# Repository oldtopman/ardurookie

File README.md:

ardurookie
====
----
A simple, cheap board for the ATmega328 chips and compatibles.

This is Open Source Hardware, CC-BY-SA 4.0

See docs/overview.txt for more information.

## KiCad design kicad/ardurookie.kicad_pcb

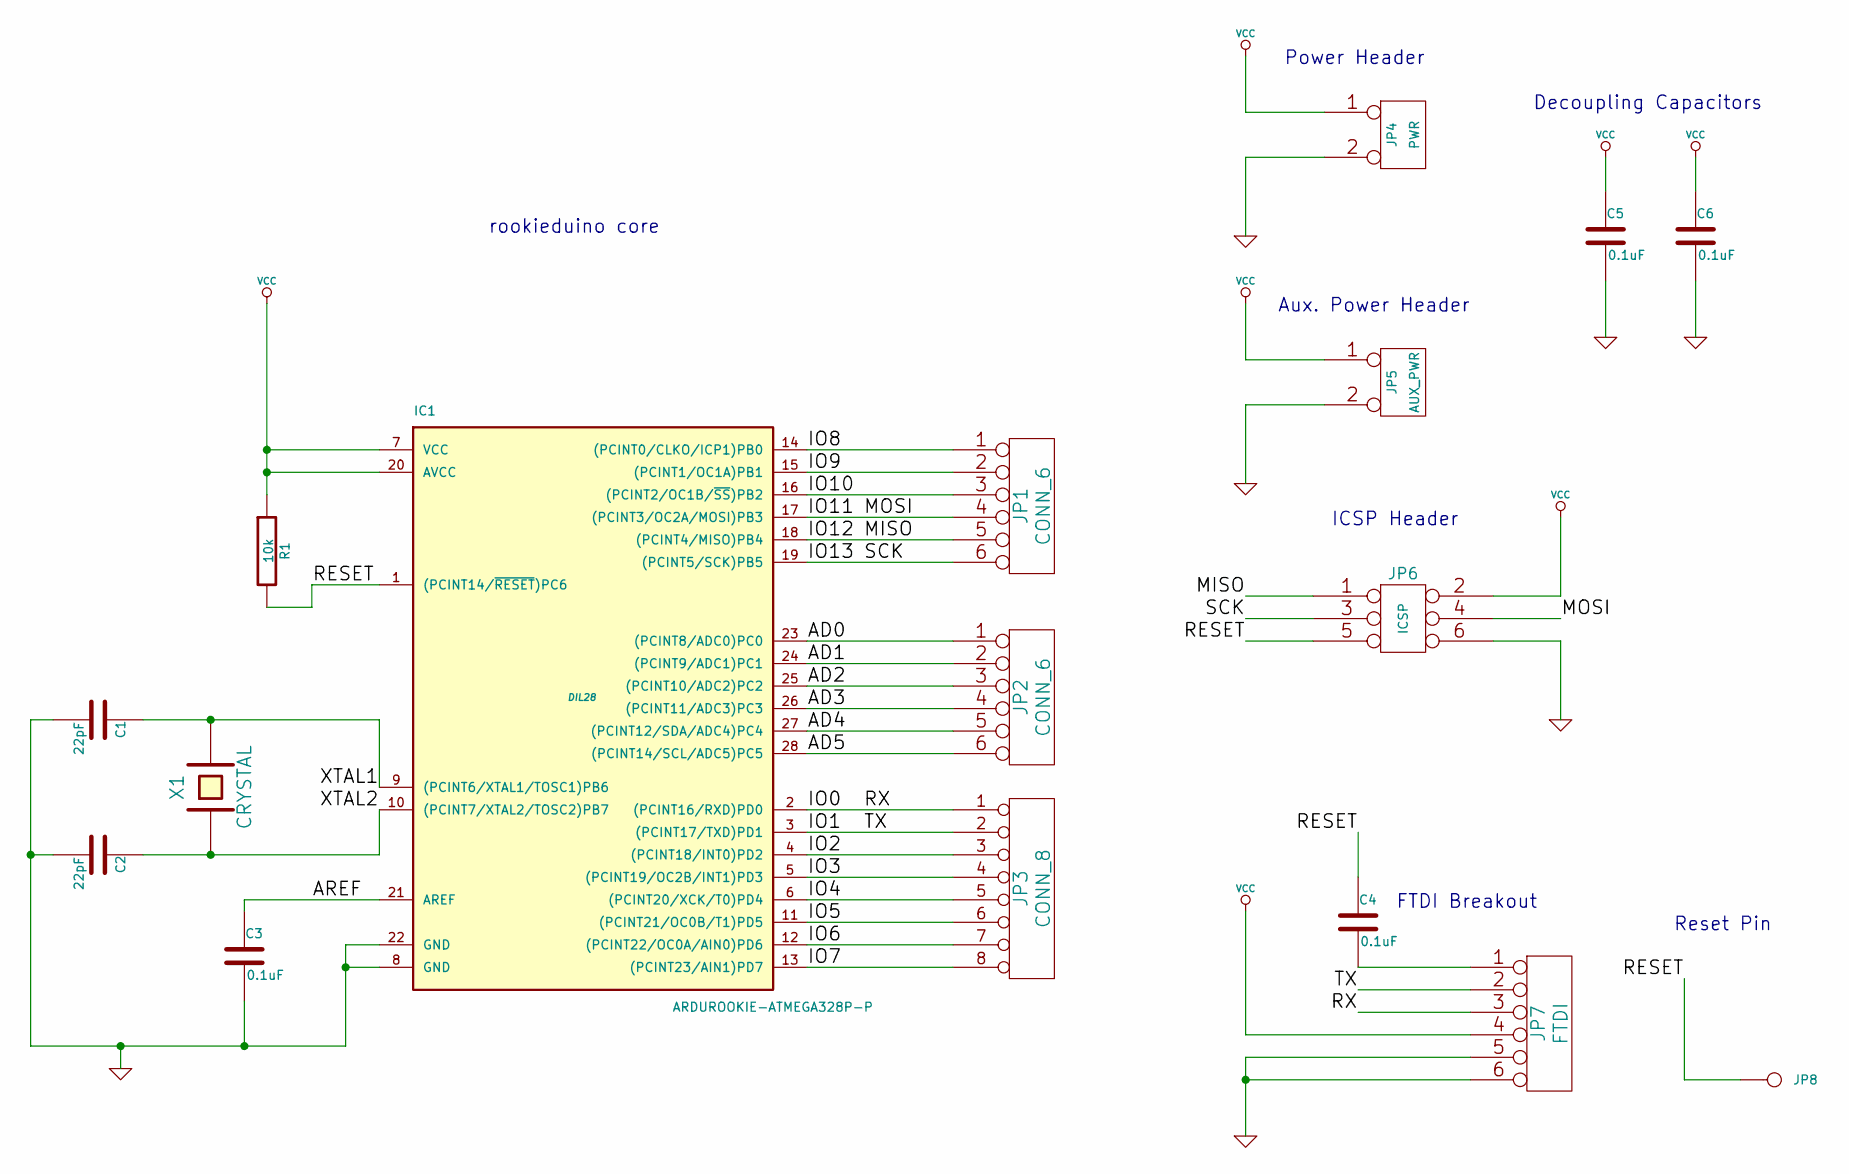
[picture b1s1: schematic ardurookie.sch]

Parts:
C1, C2: 22pF
C3, C4, C5, C6: 0.1uF
IC1: ARDUROOKIE-ATMEGA328P-P; DIL28
JP1, JP2: CONN_6
JP3: CONN_8
JP4: PWR
JP5: AUX_PWR
JP6: ICSP
JP7: FTDI
JP8: RST
R1: 10k
X1: CRYSTAL

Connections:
/AD0: IC1.23 ((PCINT8/ADC0)PC0), JP2.1
/AD1: IC1.24 ((PCINT9/ADC1)PC1), JP2.2
/AD2: IC1.25 ((PCINT10/ADC2)PC2), JP2.3
/AD3: IC1.26 ((PCINT11/ADC3)PC3), JP2.4
/AD4: IC1.27 ((PCINT12/SDA/ADC4)PC4), JP2.5
/AD5: IC1.28 ((PCINT14/SCL/ADC5)PC5), JP2.6
/AREF: C3.1, IC1.21 (AREF)
/IO0: IC1.2 ((PCINT16/RXD)PD0), JP3.1, JP7.3
/IO1: IC1.3 ((PCINT17/TXD)PD1), JP3.2, JP7.2
/IO2: IC1.4 ((PCINT18/INT0)PD2), JP3.3
/IO3: IC1.5 ((PCINT19/OC2B/INT1)PD3), JP3.4
/IO4: IC1.6 ((PCINT20/XCK/T0)PD4), JP3.5
/IO5: IC1.11 ((PCINT21/OC0B/T1)PD5), JP3.6
/IO6: IC1.12 ((PCINT22/OC0A/AIN0)PD6), JP3.7
/IO7: IC1.13 ((PCINT23/AIN1)PD7), JP3.8
/IO8: IC1.14 ((PCINT0/CLKO/ICP1)PB0), JP1.1
/IO9: IC1.15 ((PCINT1/OC1A)PB1), JP1.2
/IO10: IC1.16 ((PCINT2/OC1B/~SS~)PB2), JP1.3
/IO11: IC1.17 ((PCINT3/OC2A/MOSI)PB3), JP1.4, JP6.4
/IO12: IC1.18 ((PCINT4/MISO)PB4), JP1.5, JP6.1
/IO13: IC1.19 ((PCINT5/SCK)PB5), JP1.6, JP6.3
/RESET: C4.1, IC1.1 ((PCINT14/~RESET~)PC6), JP6.5, JP8.1, R1.2
/XTAL1: C1.1, IC1.9 ((PCINT6/XTAL1/TOSC1)PB6), X1.2
/XTAL2: C2.1, IC1.10 ((PCINT7/XTAL2/TOSC2)PB7), X1.1
GND: C1.2, C2.2, C3.2, C5.2, C6.2, IC1.8 (GND), IC1.22 (GND), JP4.2 (PM), JP5.2 (PM), JP6.6, JP7.5, JP7.6
unnamed: C4.2, JP7.1
VCC: C5.1, C6.1, IC1.7 (VCC), IC1.20 (AVCC), JP4.1, JP5.1, JP6.2, JP7.4, R1.1

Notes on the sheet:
Decoupling Capacitors
Power Header
ICSP Header
FTDI Breakout
rookieduino core
Aux. Power Header
Reset Pin

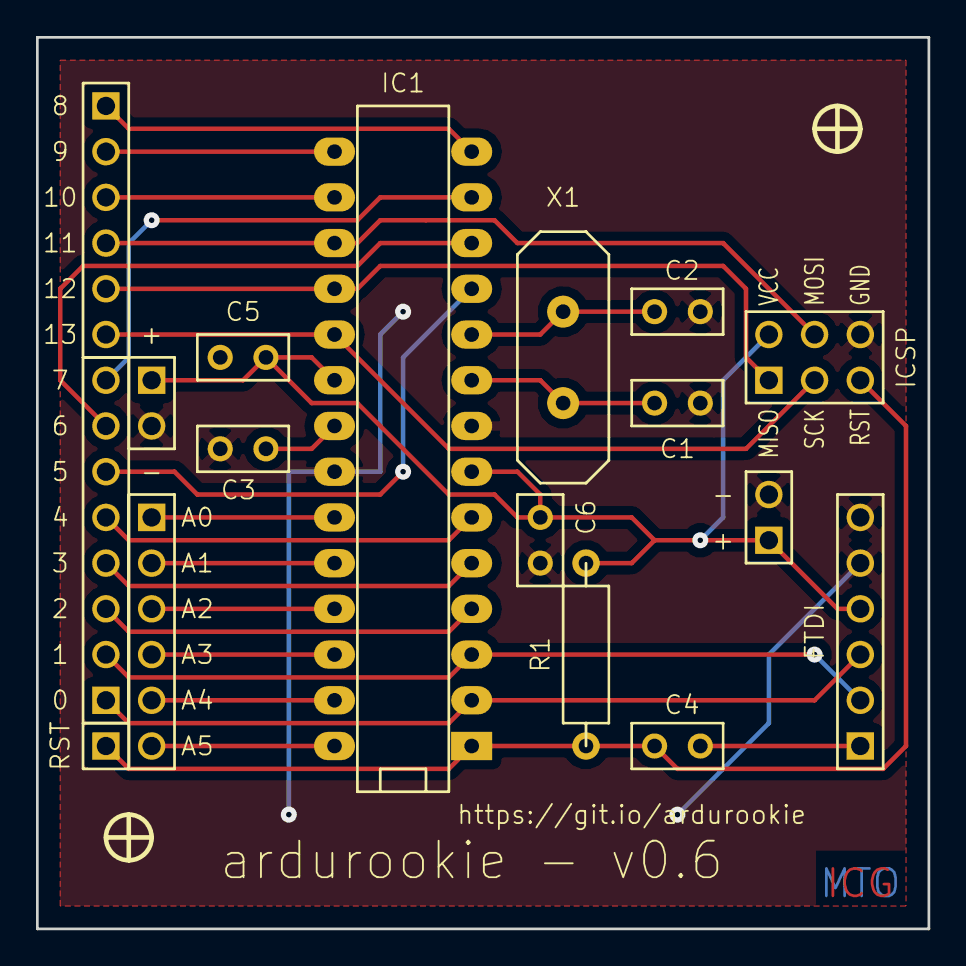
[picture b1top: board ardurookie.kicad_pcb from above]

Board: 2 copper layers, 49.5 x 49.5 mm, 17 parts (0 on the bottom side), 27 nets.

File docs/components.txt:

|<---------------------------------------------------------------------------->|

+===============+
|Component List:|
+===============+

  This is a simple breakdown of which components do what. If you can't read the
schematic, or are just too lazy, or want to know what I was thinking, this is a
great place to start.
  Components suffixed with '=' are critical to board operation, and are
non-optional.

C1-----22pF
  This is a loading capacitor (probably) for the frequency crystal.
  If you have the crystal, you need this capacitor.

C2-----22pF
  This is a loading capacitor (probably) for the frequency crystal.
  If you have the crystal, you need this capacitor.

C3=====0.1uF
  You need this for the board to be stable. I don't know how exactly this works,
but if it isn't present, the board won't work very well.

C4-----0.1uF
  This allows the FTDI boards to auto-reset the chip when you upload a sketch.
Not required, but certainly a welcome feature if you'll be using it frequently.

C5-----0.1uF
  This is a decoupling capacitor. If you have a very clean power supply *and* you
are not operating at the lower extremes of stable voltages for your chip, you
will probably be able to omit this. It also reduces emitted RF significantly.

C6-----0.1uF
  This is a decoupling capacitor. If you have a very clean power supply *and* you
are not operating at the lower extremes of stable voltages for your chip, you
will probably be able to omit this. It also reduces emitted RF significantly.


IC1====ATMEGA328P (Or similar)
  Main chip. Use the ATMEGA328 series, or any other chip that shares the pinout.
I reccommend the 328P for its low power states.

JP1----CONN_6
  Holes for connections. You can put pin-headers here, or just wire it up as you
see fit. This one is for IO8 - IO13.

JP2----CONN_6
  Holes for connections. You can put pin-headers here, or just wire it up as you
see fit. This one is for AD0 - AD5.

JP3----CONN_8
  Holes for connections. You can put pin-headers here, or just wire it up as you
see fit. This one is for IO0 - IO7.

JP4----PWR
  This is a power header, conviently located near the other IO pins.

JP5----AUX_PWR
  This is a power header, conviently located away from the IO pins.

JP6----ICSP
  This port should be populated with standard 0.1" male header pins. It is
designed to be a standard ICSP pinout, so the bootloader can be changed with
the chip still soldered into the board.

JP7----FTDI
  This port should be populated with standard 0.1" male header pins. It is
designed to be compatible with Sparkfun's FTDI breakouts.
https://www.sparkfun.com/products/9716

JP8----RST
  This is a hole for reset. You can put a pin-header here, or just wire it up as
you see fit.

R1=====10k
  This prevents the board from going into reset while you're trying to use it.
This component can't really be omitted, though the value is fairly flexible.

X1-----CRYSTAL
  This is an external crystal for the ATMEGA. If you decide to use this component,
be sure to populate both C1 and C2 on the board.

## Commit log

2014-11-29 v0.6 release
2014-12-09 Updated documentation, added images.
2014-12-09 Tweaked the readme.
